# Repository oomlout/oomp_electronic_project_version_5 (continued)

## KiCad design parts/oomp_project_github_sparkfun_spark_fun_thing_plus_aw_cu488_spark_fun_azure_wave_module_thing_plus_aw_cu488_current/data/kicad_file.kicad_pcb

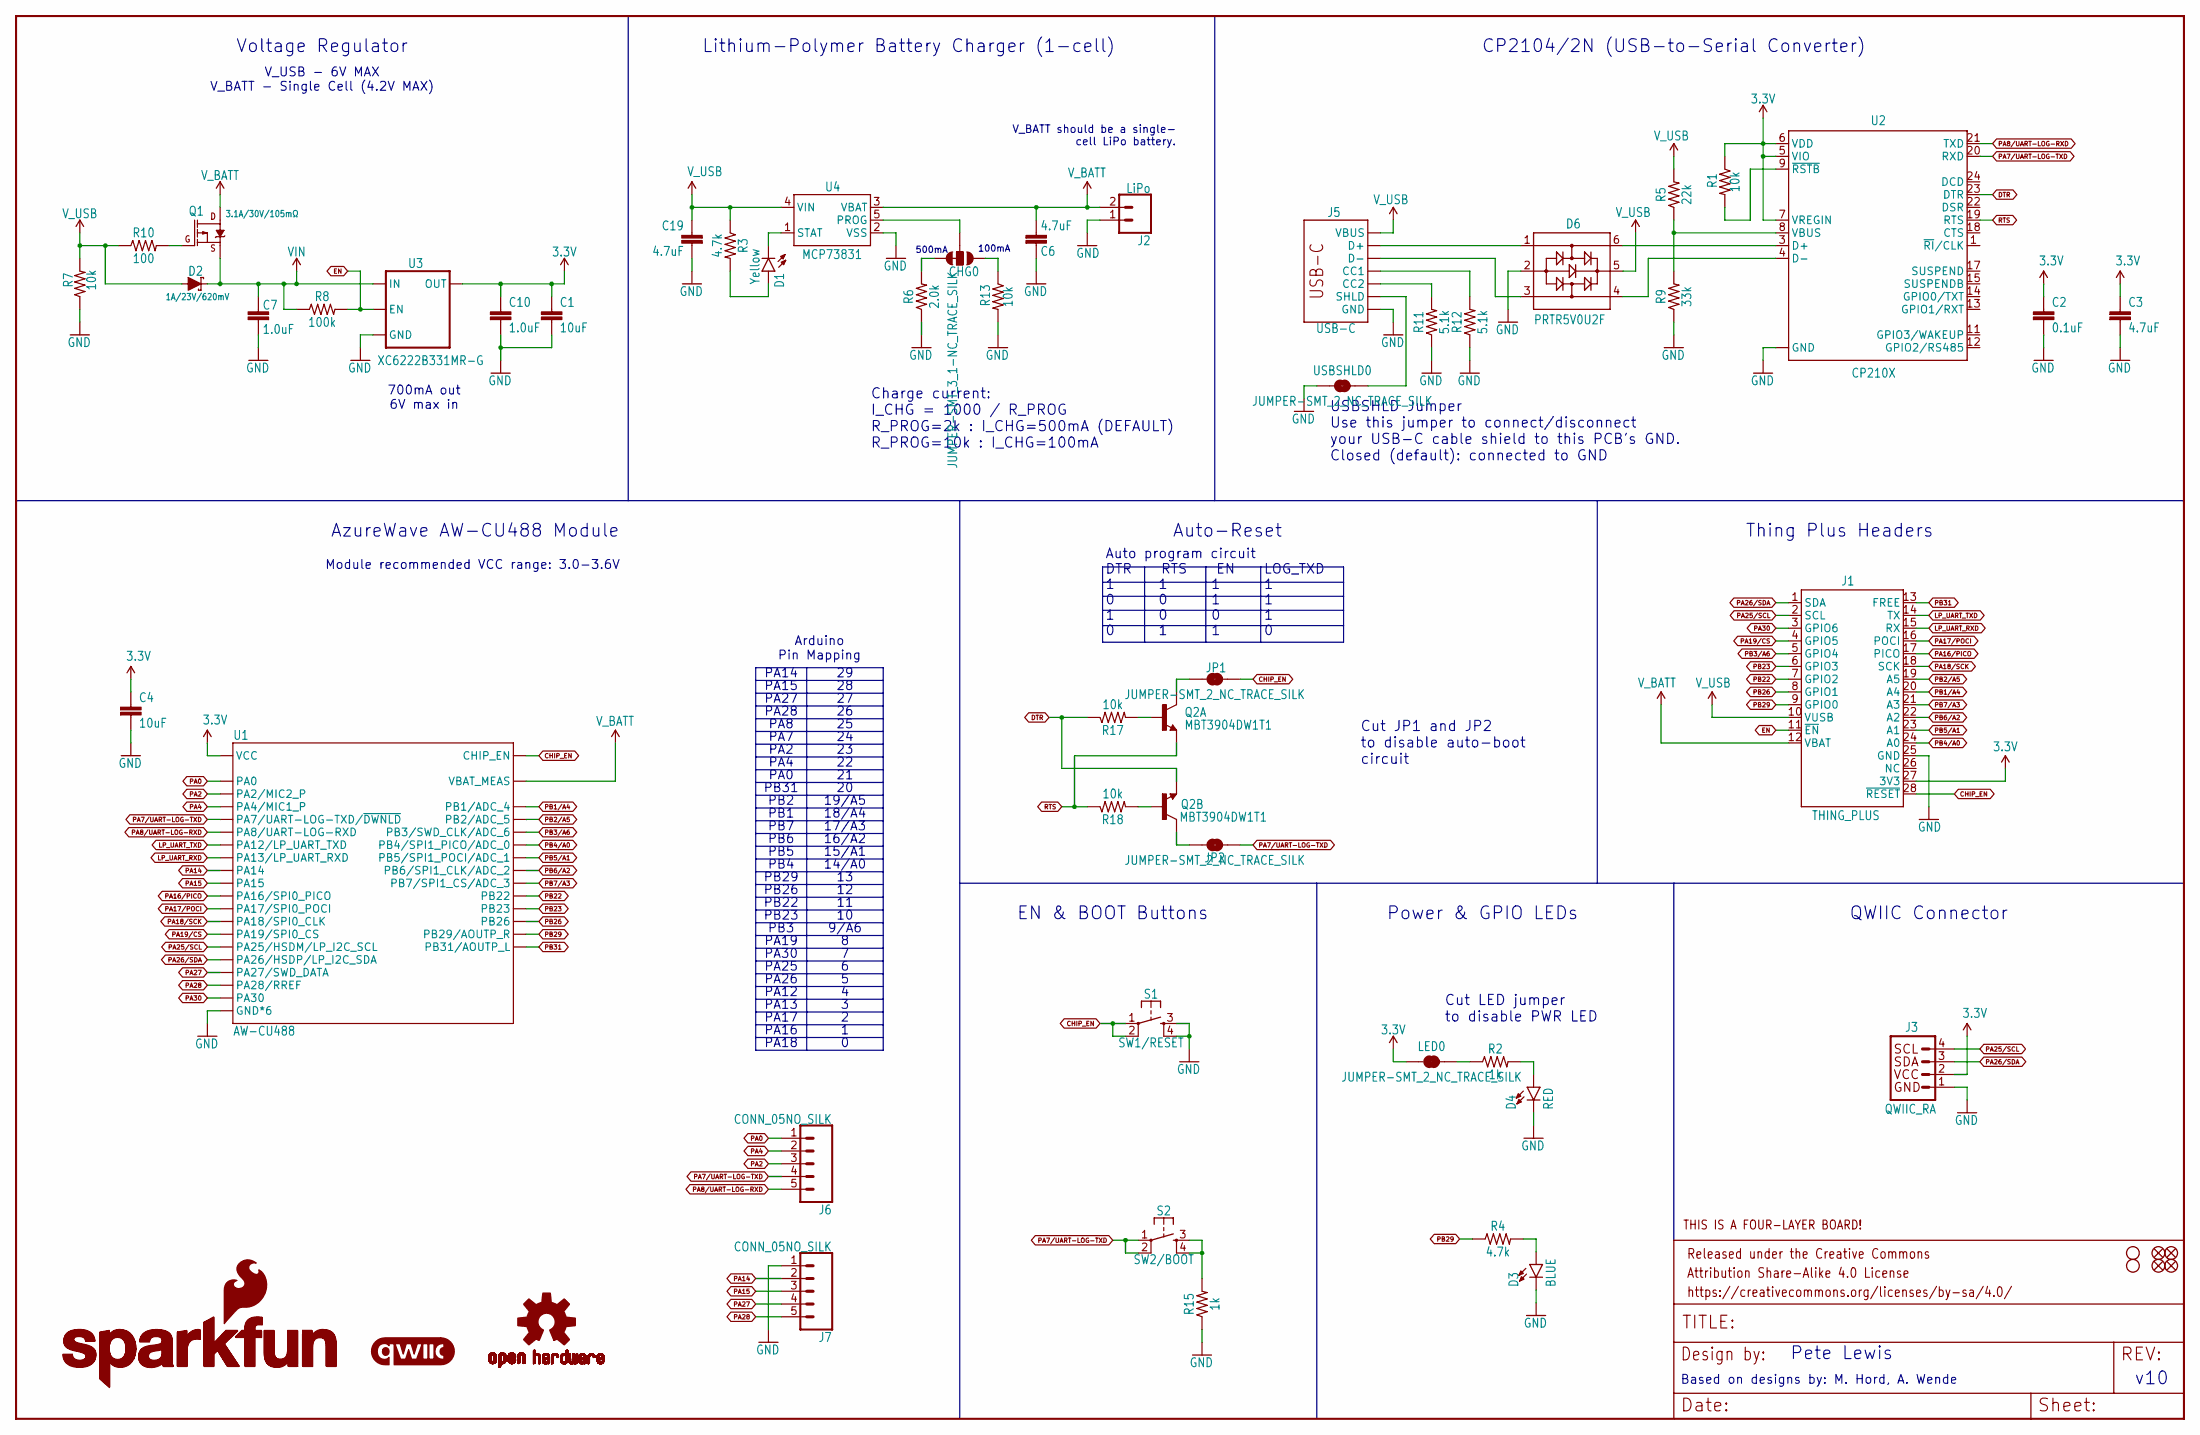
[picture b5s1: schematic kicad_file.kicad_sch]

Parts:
C1: 10uF; 0402-TIGHT
C2: 0.1uF; 0402-TIGHT
C3, C6, C19: 4.7uF; 0402-TIGHT
C4: 10uF; 0603
C7, C10: 1.0uF; 0402-TIGHT
CHG0: JUMPER-SMT_3_1-NC_TRACE_SILK; SMT-JUMPER_3_1-NC_TRACE_SILK
D1: Yellow; LED-0603
D2: 1A/23V/620mV; SOD-323
D3: BLUE; LED-0603
D4: RED; LED-0603
D6: PRTR5V0U2F; SOT886
FD1, FD2, FD3, FD4: FIDUCIALUFIDUCIAL; FIDUCIAL-MICRO
FRAME1: FRAME-LEDGER; CREATIVE_COMMONS
H1, H2: STAND-OFF
J1: THING_PLUS
J2: LiPo; JST-2-SMD
J3: QWIIC_RA; JST04_1MM_RA
J5: USB-C; USB-C-16P-4LAYER-ISOLATED
J6, J7: CONN_05NO_SILK; 1X05_NO_SILK
JP1, JP2: JUMPER-SMT_2_NC_TRACE_SILK; SMT-JUMPER_2_NC_TRACE_SILK
LED0: JUMPER-SMT_2_NC_TRACE_SILK; SMT-JUMPER_2_NC_TRACE_SILK
LOGO1: SFE_LOGO_NAME.1_INCH; SFE_LOGO_NAME_.1
LOGO2: OSHW-LOGOMINI; OSHW-LOGO-MINI
LOGO3: SFE_LOGO_NAME_FLAME.1_INCH; SFE_LOGO_NAME_FLAME_.1
LOGO4: FOUR_LAYER_WARNING
LOGO6: QWIIC_LOGO_4MM; QWIIC_4MM
Q1: 3.1A/30V/105mΩ; SOT23-3
Q2: MBT3904DW1T1; SC70-6
R1, R7, R13, R17, R18: 10k; 0402-TIGHT
R2, R15: 1k; 0402-TIGHT
R3, R4: 4.7k; 0402-TIGHT
R5: 22k; 0402-TIGHT
R6: 2.0k; 0603
R8: 100k; 0402-TIGHT
R9: 33k; 0402-TIGHT
R10: 100; 0402-TIGHT
R11, R12: 5.1k; 0402-TIGHT
S1: SW1/RESET; TACTILE_SWITCH_SMD_4.6X2.8MM
S2: SW2/BOOT; TACTILE_SWITCH_SMD_4.6X2.8MM
U1: AW-CU488; LGA150_AW-CU488
U2: CP210X; QFN24
U3: XC6222B331MR-G; SOT23-5
U4: MCP73831; SOT23-5
USBSHLD0: JUMPER-SMT_2_NC_TRACE_SILK; SMT-JUMPER_2_NC_TRACE_SILK

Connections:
3.3V: C1.1, C2.1, C3.1, C4.1, C10.1, J1.27 (3V3), J3.2, LED0.1, R1.1, U1.F1 (VCC), U2.5 (VIO), U2.6 (VDD), U2.7 (VREGIN), U3.5 (OUT)
CC1: J5.A5 (CC1), R12.2
CC2: J5.B5 (CC2), R11.2
CHG: D1.C, U4.1 (STAT)
CHIP_EN: J1.28 (~RESET), JP1.2, S1.1, S1.2, U1.K11 (CHIP_EN)
DTR: Q2.1 (E), R17.1, U2.23 (DTR)
EN: J1.11 (~EN), R8.2, U3.3 (EN)
GND: C1.2, C2.2, C3.2, C4.2, C6.2, C7.2, C10.2, C19.2, D3.C, D4.C, D6.2, J1.25 (GND), J2.1 (2), J3.1, J5.GND, J5.GND2 (GND), J7.1, R6.1, R7.1, R9.1, R11.1, R12.1, R13.2, R15.1, S1.3, S1.4, U1.A1 (GND*6), U1.A2 (GND*6), U1.A14 (GND*6), U1.A15 (GND*6), U1.B14 (GND*6), U1.B15 (GND*6), U1.C3 (GND*6), U1.C4 (GND*6), U1.C5 (GND*6), U1.C6 (GND*6), U1.C7 (GND*6), U1.C8 (GND*6), U1.C9 (GND*6), U1.C10 (GND*6), U1.C11 (GND*6), U1.C12 (GND*6), U1.C13 (GND*6), U1.C14 (GND*6), U1.C15 (GND*6), U1.D3 (GND*6), U1.D4 (GND*6), U1.D5 (GND*6), U1.D6 (GND*6), U1.D7 (GND*6), U1.D8 (GND*6), U1.D9 (GND*6), U1.D10 (GND*6), U1.D11 (GND*6), U1.D12 (GND*6), U1.D13 (GND*6), U1.D14 (GND*6), U1.D15 (GND*6), U1.E1 (GND*6), U1.E2 (GND*6), U1.E3 (GND*6), U1.E4 (GND*6), U1.E5 (GND*6), U1.E6 (GND*6), U1.E7 (GND*6), U1.E8 (GND*6), U1.E9 (GND*6), U1.E10 (GND*6), U1.E11 (GND*6), U1.E12 (GND*6), U1.E13 (GND*6), U1.E14 (GND*6), U1.E15 (GND*6), U1.F2 (GND*6), U1.F3 (GND*6), U1.F4 (GND*6), U1.F5 (GND*6), U1.F6 (GND*6), U1.F7 (GND*6), U1.F8 (GND*6), U1.F9 (GND*6), U1.F10 (GND*6), U1.F11 (GND*6), U1.F12 (GND*6), U1.F13 (GND*6), U1.F14 (GND*6), U1.F15 (GND*6), U1.G1 (GND*6), U1.G2 (GND*6), U1.G3 (GND*6), U1.G4 (GND*6), U1.G5 (GND*6), U1.G6 (GND*6), U1.G7 (GND*6), U1.G8 (GND*6), U1.G9 (GND*6), U1.G10 (GND*6), U1.G11 (GND*6), U1.G12 (GND*6), U1.G13 (GND*6), U1.G14 (GND*6), U1.G15 (GND*6), U1.H3 (GND*6), U1.H4 (GND*6), U1.H5 (GND*6), U1.H6 (GND*6), U1.H7 (GND*6), U1.H8 (GND*6), U1.H9 (GND*6), U1.H10 (GND*6), U1.H11 (GND*6), U1.H12 (GND*6), U1.H13 (GND*6), U1.H14 (GND*6), U1.H15 (GND*6), U1.J14 (GND*6), U1.J15 (GND*6), U1.K3 (GND*6), U1.K4 (GND*6), U1.K14 (GND*6), U1.K15 (GND*6), U2.2 (GND), U2.PAD (GND), U3.2 (GND), U4.2 (VSS), USBSHLD0.1
LP_UART_RXD: J1.15 (RX), U1.B13 (PA13/LP_UART_RXD)
LP_UART_TXD: J1.14 (TX), U1.A13 (PA12/LP_UART_TXD)
unnamed: R1.2, U2.9 (~RSTB)
unnamed: D3.A, R4.2
unnamed: Q2.5 (B), R17.2
unnamed: R5.1, R9.2, U2.8 (VBUS)
unnamed: Q2.2 (B), R18.2
unnamed: JP1.1, Q2.3 (C)
unnamed: Q1.1 (G), R10.2
unnamed: R15.2, S2.3, S2.4
unnamed: CHG0.2, U4.5 (PROG)
unnamed: JP2.1, Q2.6 (C)
unnamed: CHG0.1, R13.1
unnamed: LED0.2, R2.1
unnamed: CHG0.3, R6.2
unnamed: D4.A, R2.2
unnamed: D6.6, U2.3 (D+)
unnamed: D6.1, J5.A6 (D+), J5.B6 (D+)
unnamed: D1.A, R3.2
unnamed: D6.4, U2.4 (D-)
unnamed: D6.3, J5.A7 (D-), J5.B7 (D-)
PA0: J6.1, U1.K8 (PA0)
PA2: J6.3, U1.K10 (PA2/MIC2_P)
PA4: J6.2, U1.K9 (PA4/MIC1_P)
PA7/UART-LOG-TXD: J6.4, JP2.2, S2.1, S2.2, U1.K12 (PA7/UART-LOG-TXD/~DWNLD), U2.20 (RXD)
PA8/UART-LOG-RXD: J6.5, U1.K13 (PA8/UART-LOG-RXD), U2.21 (TXD)
PA14: J7.2, U1.A12 (PA14)
PA15: J7.3, U1.B12 (PA15)
PA16/PICO: J1.17 (PICO), U1.A11 (PA16/SPI0_PICO)
PA17/POCI: J1.16 (POCI), U1.B11 (PA17/SPI0_POCI)
PA18/SCK: J1.18 (SCK), U1.A10 (PA18/SPI0_CLK)
PA19/CS: J1.4 (GPIO5), U1.B10 (PA19/SPI0_CS)
PA25/SCL: J1.2 (SCL), J3.4, U1.A5 (PA25/HSDM/LP_I2C_SCL)
PA26/SDA: J1.1 (SDA), J3.3, U1.A6 (PA26/HSDP/LP_I2C_SDA)
PA27: J7.4, U1.A9 (PA27/SWD_DATA)
PA28: J7.5, U1.A7 (PA28/RREF)
PA30: J1.3 (GPIO6), U1.A8 (PA30)
PB1/A4: J1.20 (A4), U1.A3 (PB1/ADC_4)
PB2/A5: J1.19 (A5), U1.A4 (PB2/ADC_5)
PB3/A6: J1.5 (GPIO4), U1.B1 (PB3/SWD_CLK/ADC_6)
PB4/A0: J1.24 (A0), U1.B2 (PB4/SPI1_PICO/ADC_0)
PB5/A1: J1.23 (A1), U1.C1 (PB5/SPI1_POCI/ADC_1)
PB6/A2: J1.22 (A2), U1.C2 (PB6/SPI1_CLK/ADC_2)
PB7/A3: J1.21 (A3), U1.D1 (PB7/SPI1_CS/ADC_3)
PB22: J1.7 (GPIO2), U1.K1 (PB22)
PB23: J1.6 (GPIO3), U1.K2 (PB23)
PB26: J1.8 (GPIO1), U1.K5 (PB26)
PB29: J1.9 (GPIO0), R4.1, U1.K6 (PB29/AOUTP_R)
PB31: J1.13 (FREE), U1.K7 (PB31/AOUTP_L)
RTS: Q2.4 (E), R18.1, U2.19 (RTS)
USB_SHLD: J5.SHLD1 (SHLD), J5.SHLD2 (SHLD), J5.SHLD3 (SHLD), J5.SHLD4 (SHLD), J5.SHLD5 (SHLD), J5.SHLD6 (SHLD), J5.SHLD7 (SHLD), J5.SHLD8 (SHLD), USBSHLD0.2
VIN: C7.1, D2.C, Q1.2 (S), R8.1, U3.1 (IN)
V_BATT: C6.1, J1.12 (VBAT), J2.2 (1), Q1.3 (D), U1.D2 (VBAT_MEAS), U4.3 (VBAT)
V_USB: C19.1, D2.A, D6.5, J1.10 (VUSB), J5.VBUS1 (VBUS), J5.VBUS2 (VBUS), R3.1, R5.2, R7.2, R10.1, U4.4 (VIN)

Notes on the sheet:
PA4
PB7
PA18
500mA
PB26
PB5
PA16
PB6
Power & GPIO LEDs
v10
PA15
Arduino Pin Mapping
Lithium-Polymer Battery Charger (1-cell)
100mA
PA27
Cut LED jumper to disable PWR LED
Cut JP1 and JP2 to disable auto-boot circuit
V_BATT should be a single- cell LiPo battery.
EN & BOOT Buttons
PA30
PB4
Module recommended VCC range: 3.0-3.6V
19/A5
Voltage Regulator
Pete Lewis
700mA out 6V max in
PA7
9/A6
PB29
PB22
PB31
PA28
PB23
15/A1
PA12
16/A2
QWIIC Connector
Auto-Reset
CP2104/2N (USB-to-Serial Converter)
USBSHLD Jumper Use this jumper to connect/disconnect your USB-C cable shield to this PCB's GND. Closed (default): connected to GND

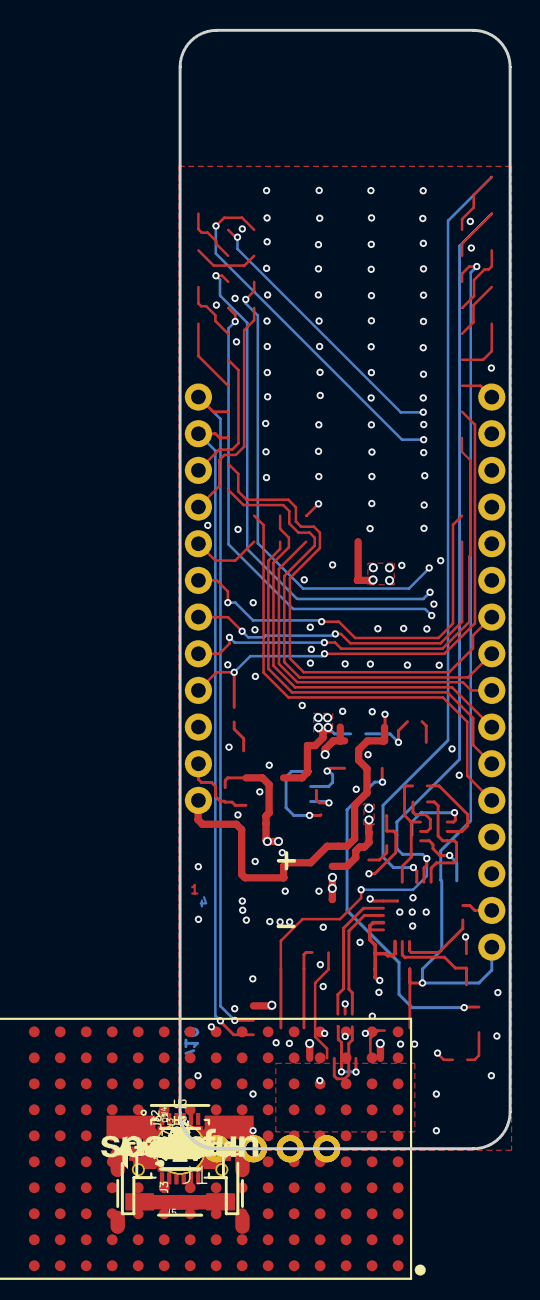
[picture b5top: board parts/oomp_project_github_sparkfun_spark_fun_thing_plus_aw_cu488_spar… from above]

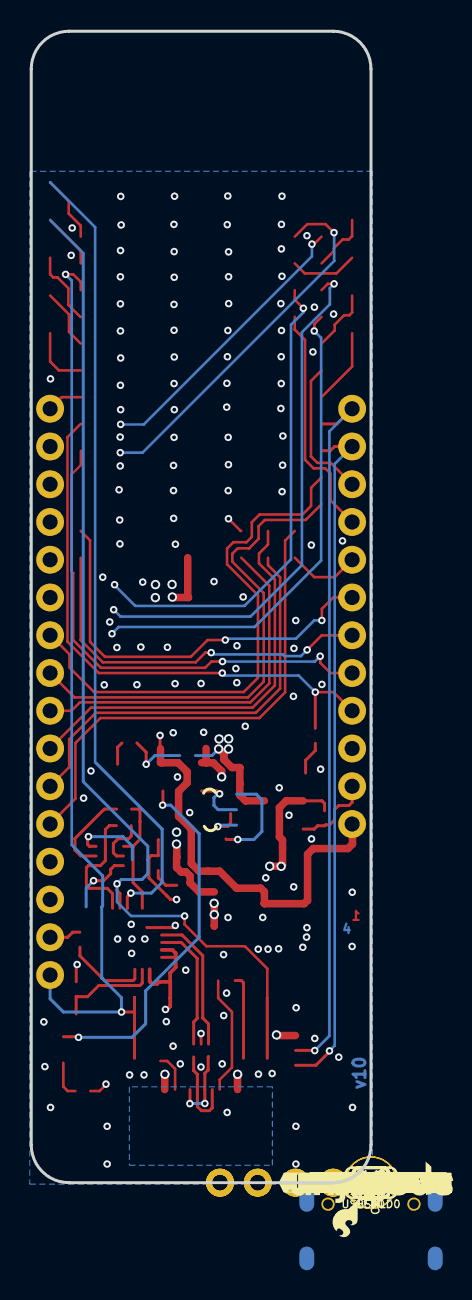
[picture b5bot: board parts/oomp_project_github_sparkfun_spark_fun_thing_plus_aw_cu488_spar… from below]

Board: 4 copper layers, 22.9 x 77.5 mm, 128 parts (57 on the bottom side), 62 nets.

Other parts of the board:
U$1: #10#30
U$2: BOOT0
U$3, U$78: CHG0
U$4: #500#0
U$5: #11#30
U$6, U$8: AZUREWAVE0
U$7: 1330
U$9, U$27: AW#CU488_0
U$10, U$62: THING_PLUS_0
U$11: MA0
U$12: #12#30
U$14: #13#30
U$15: #JP1#1
U$16: #0#1
U$18: #A0#30
U$19: #JP2#4
U$20: #USBSHLD#GND#3
U$23: PWR0
U$29: #LED#0
U$32, U$86: #GND#0
U$41: #VUSB#0
U$42: #VBAT#0
U$43: #EN#0
U$45: #3V3#0
U$46: ##RESET##0
U$48: #4#TX1#14
U$49: #3#RX1#14
U$50: #2#POCI#14
U$53: #A1#6
U$54: #A2#6
U$55: #A3#6
U$56: #A4#6
U$57: #A5#6
U$59: ORDERING_INSTRUCTIONS
U$60: #100#0
U$64: #1#PICO#14
U$67: #13#14
U$68: #12#14
U$69: #11#14
U$70: #10#14
U$71: #9#A6#14
U$72: #8#CS#14
U$73: #7#14
U$74: #6#SCL#14
U$75: #5#SDA#14
U$76: #0#SCK#14
U$77: #14#A0#15
U$79: RESET0
U$80: #15#A1#15
U$81: #16#A2#16
U$82: #17#A3#17
U$83: #18#A4#18
U$84: #19#A5#19
U$85: #20#20
U$87: #21#21
U$88: #22#22
U$89: #23#23
U$90: #24#TX#24
U$91: #25#RX#25
U$92: #26#26
U$93: #27#27
U$94: #28#28
U$95: #29#29

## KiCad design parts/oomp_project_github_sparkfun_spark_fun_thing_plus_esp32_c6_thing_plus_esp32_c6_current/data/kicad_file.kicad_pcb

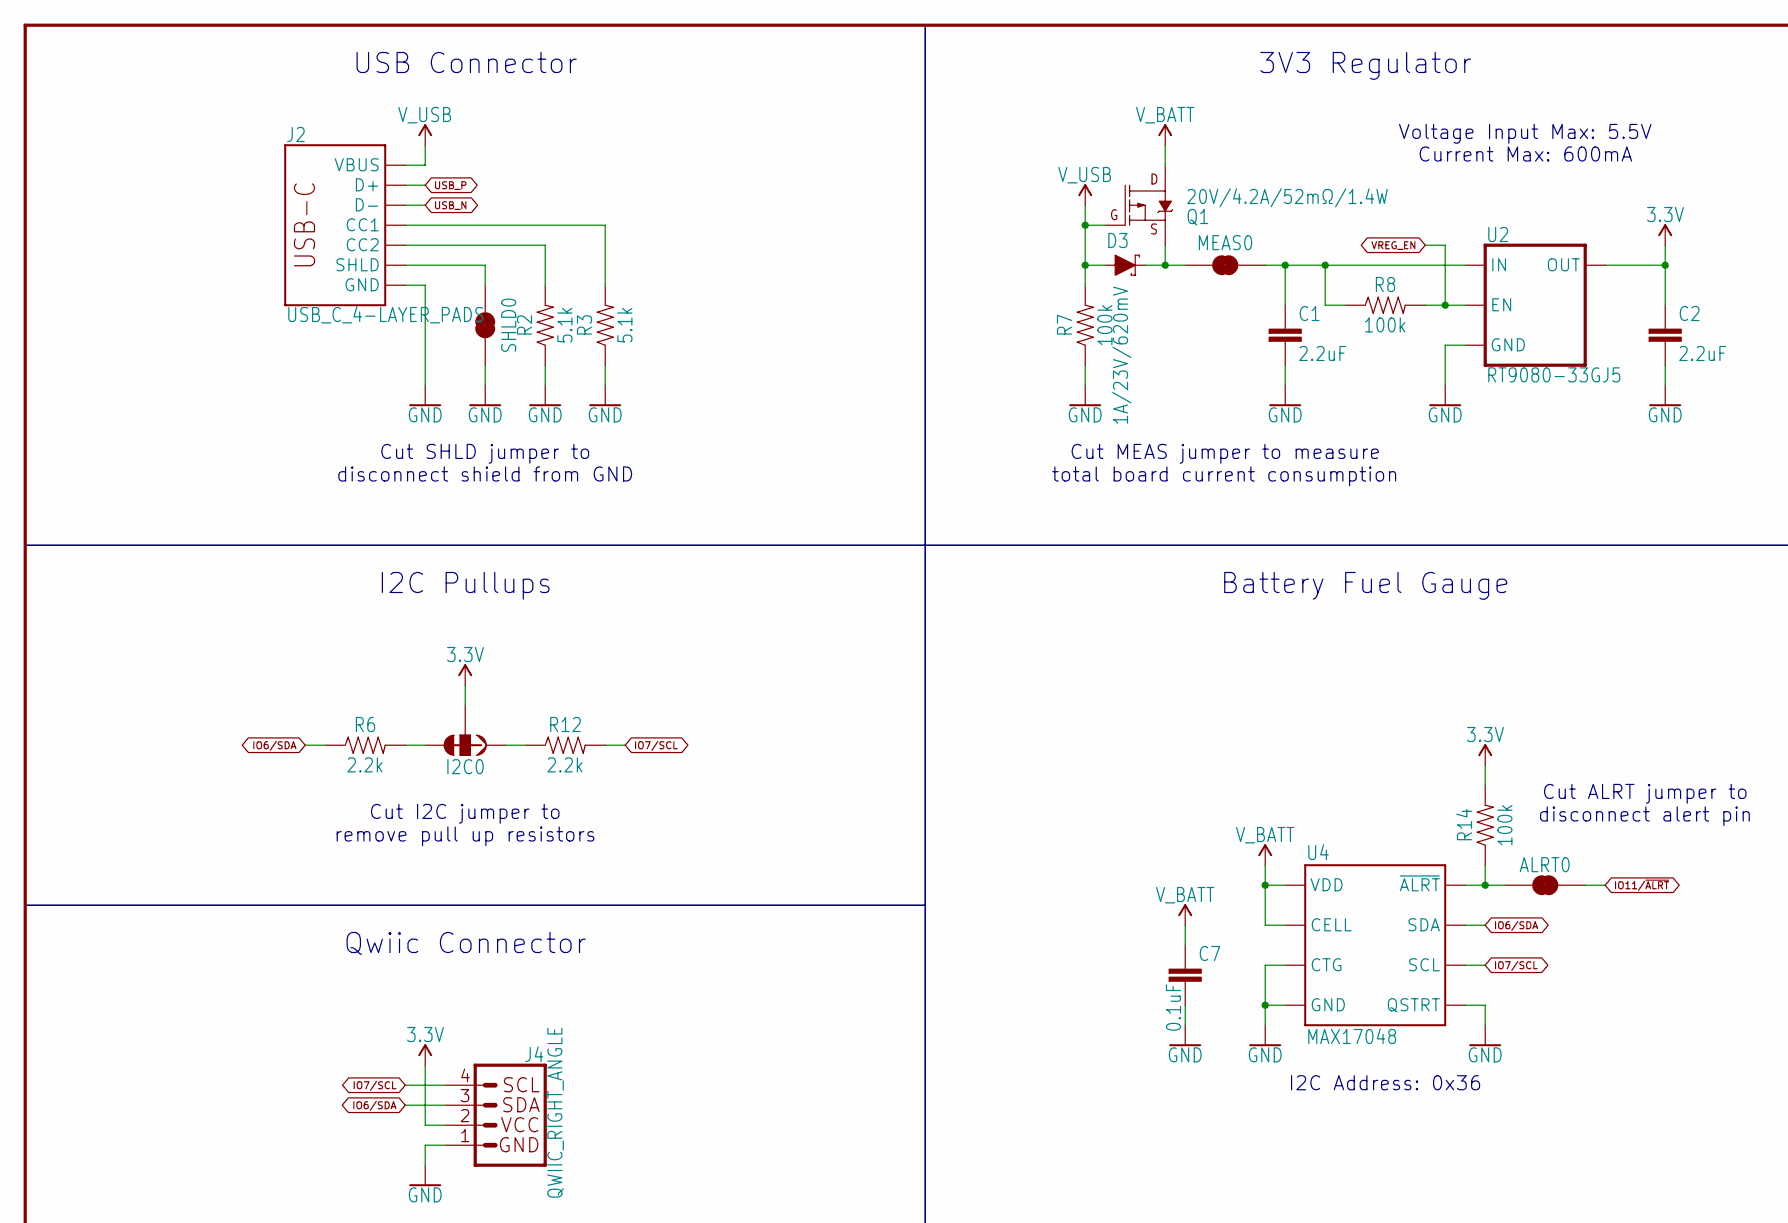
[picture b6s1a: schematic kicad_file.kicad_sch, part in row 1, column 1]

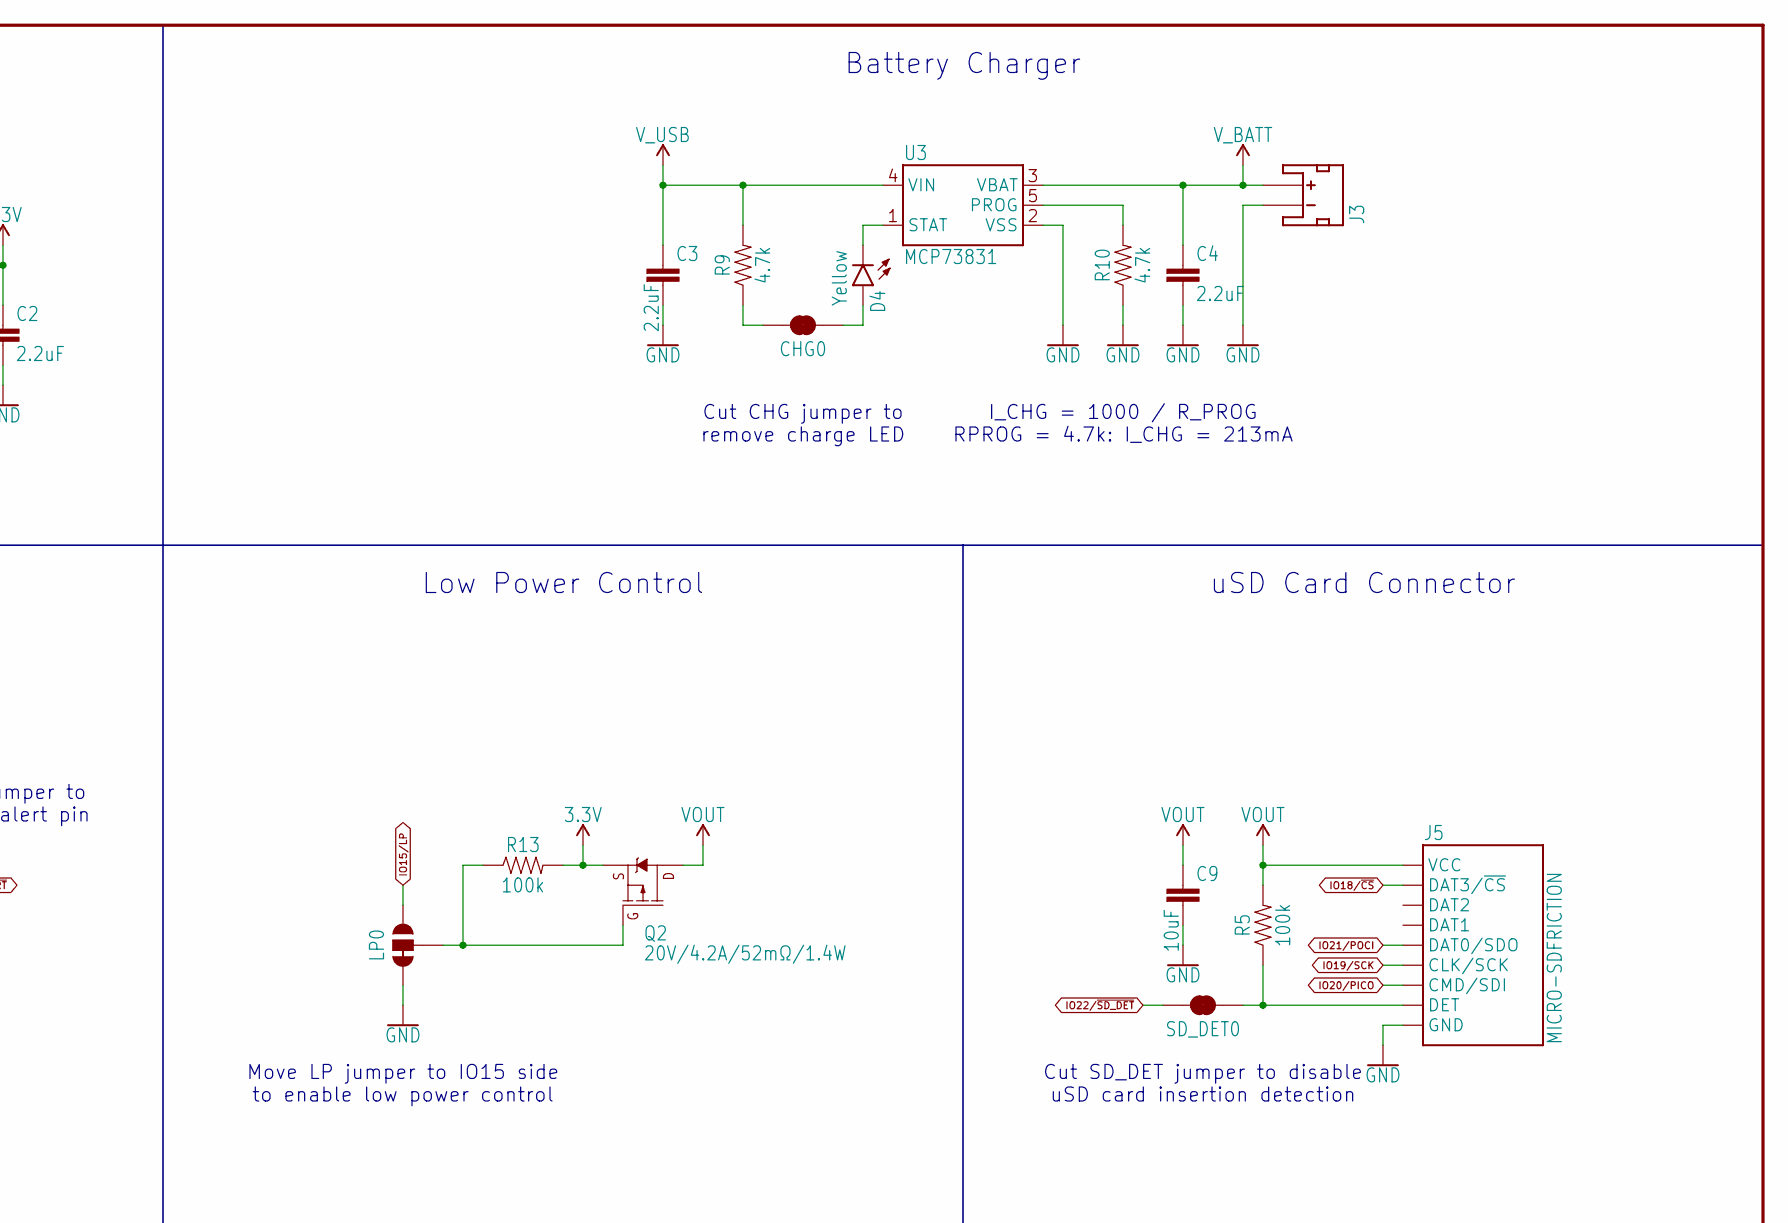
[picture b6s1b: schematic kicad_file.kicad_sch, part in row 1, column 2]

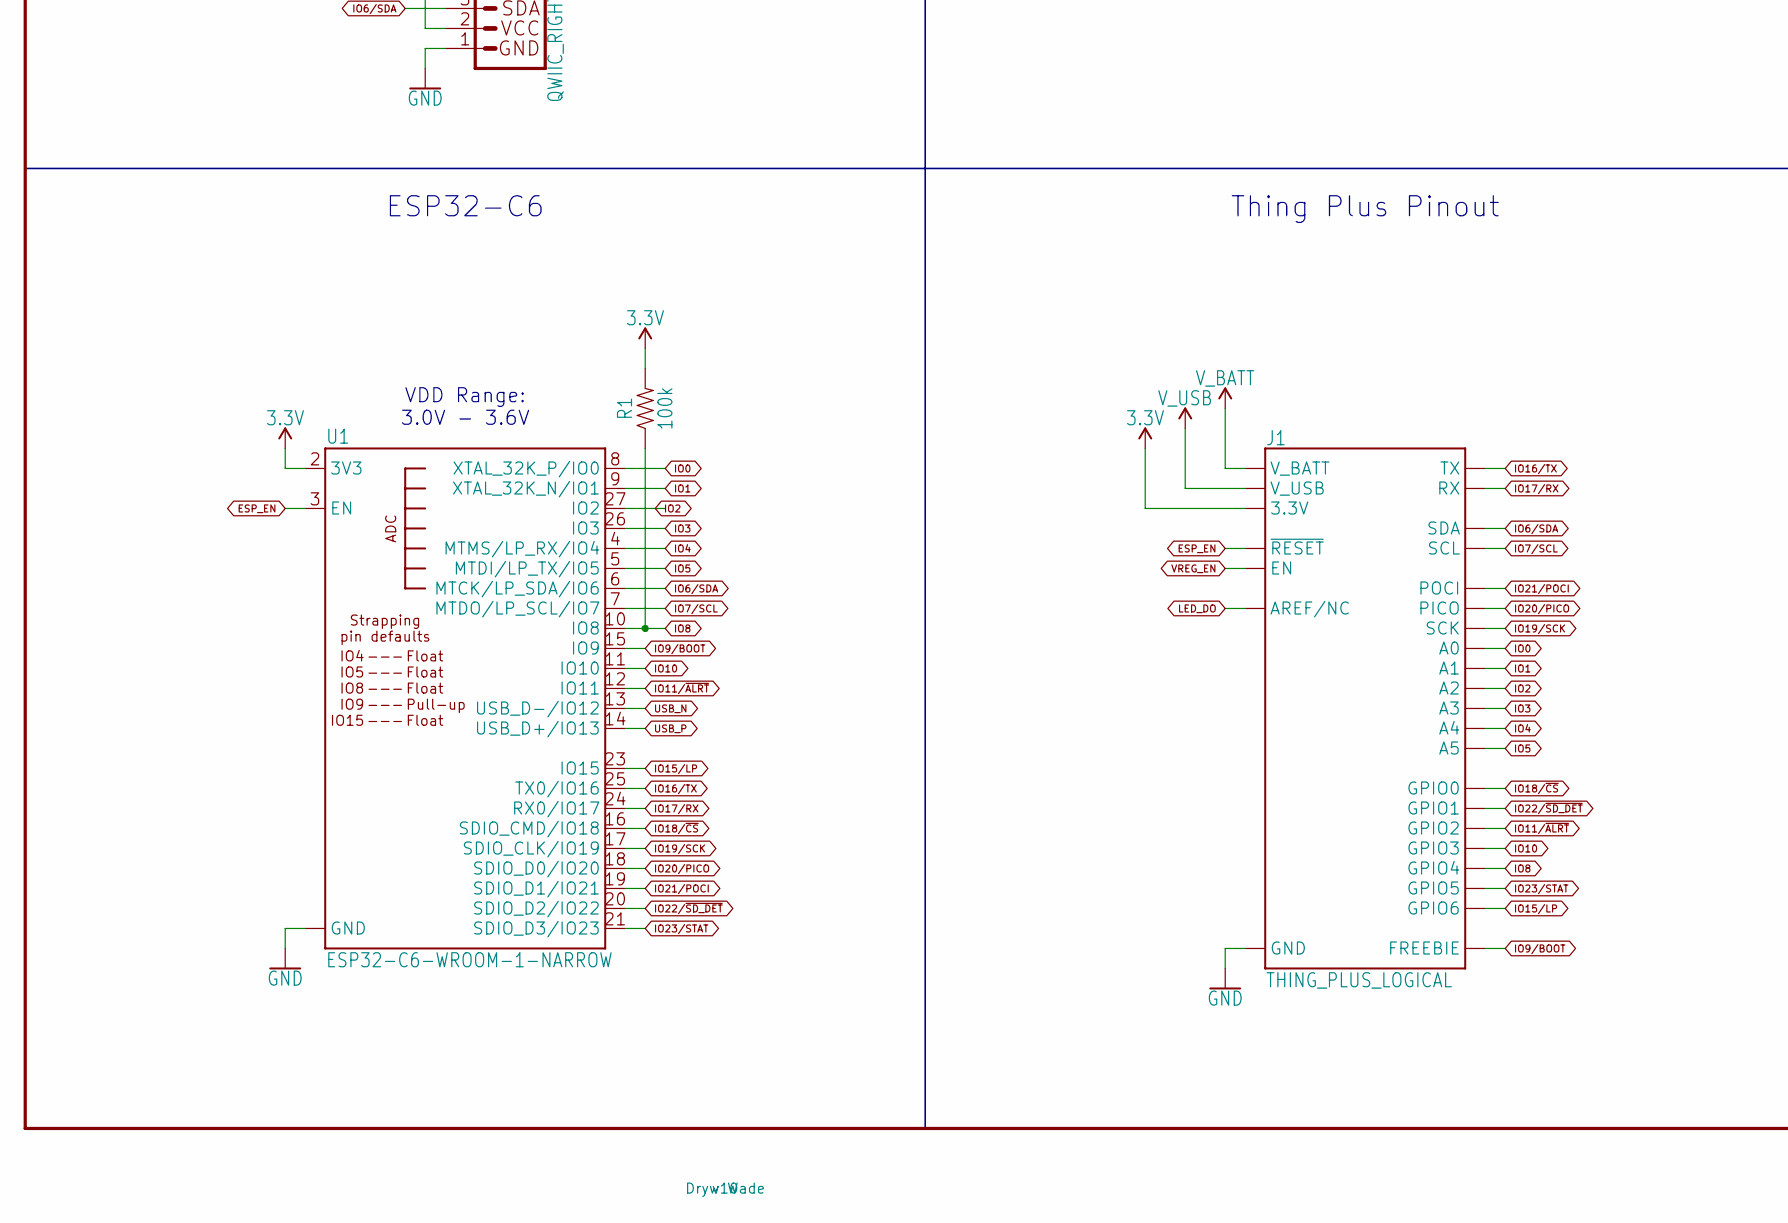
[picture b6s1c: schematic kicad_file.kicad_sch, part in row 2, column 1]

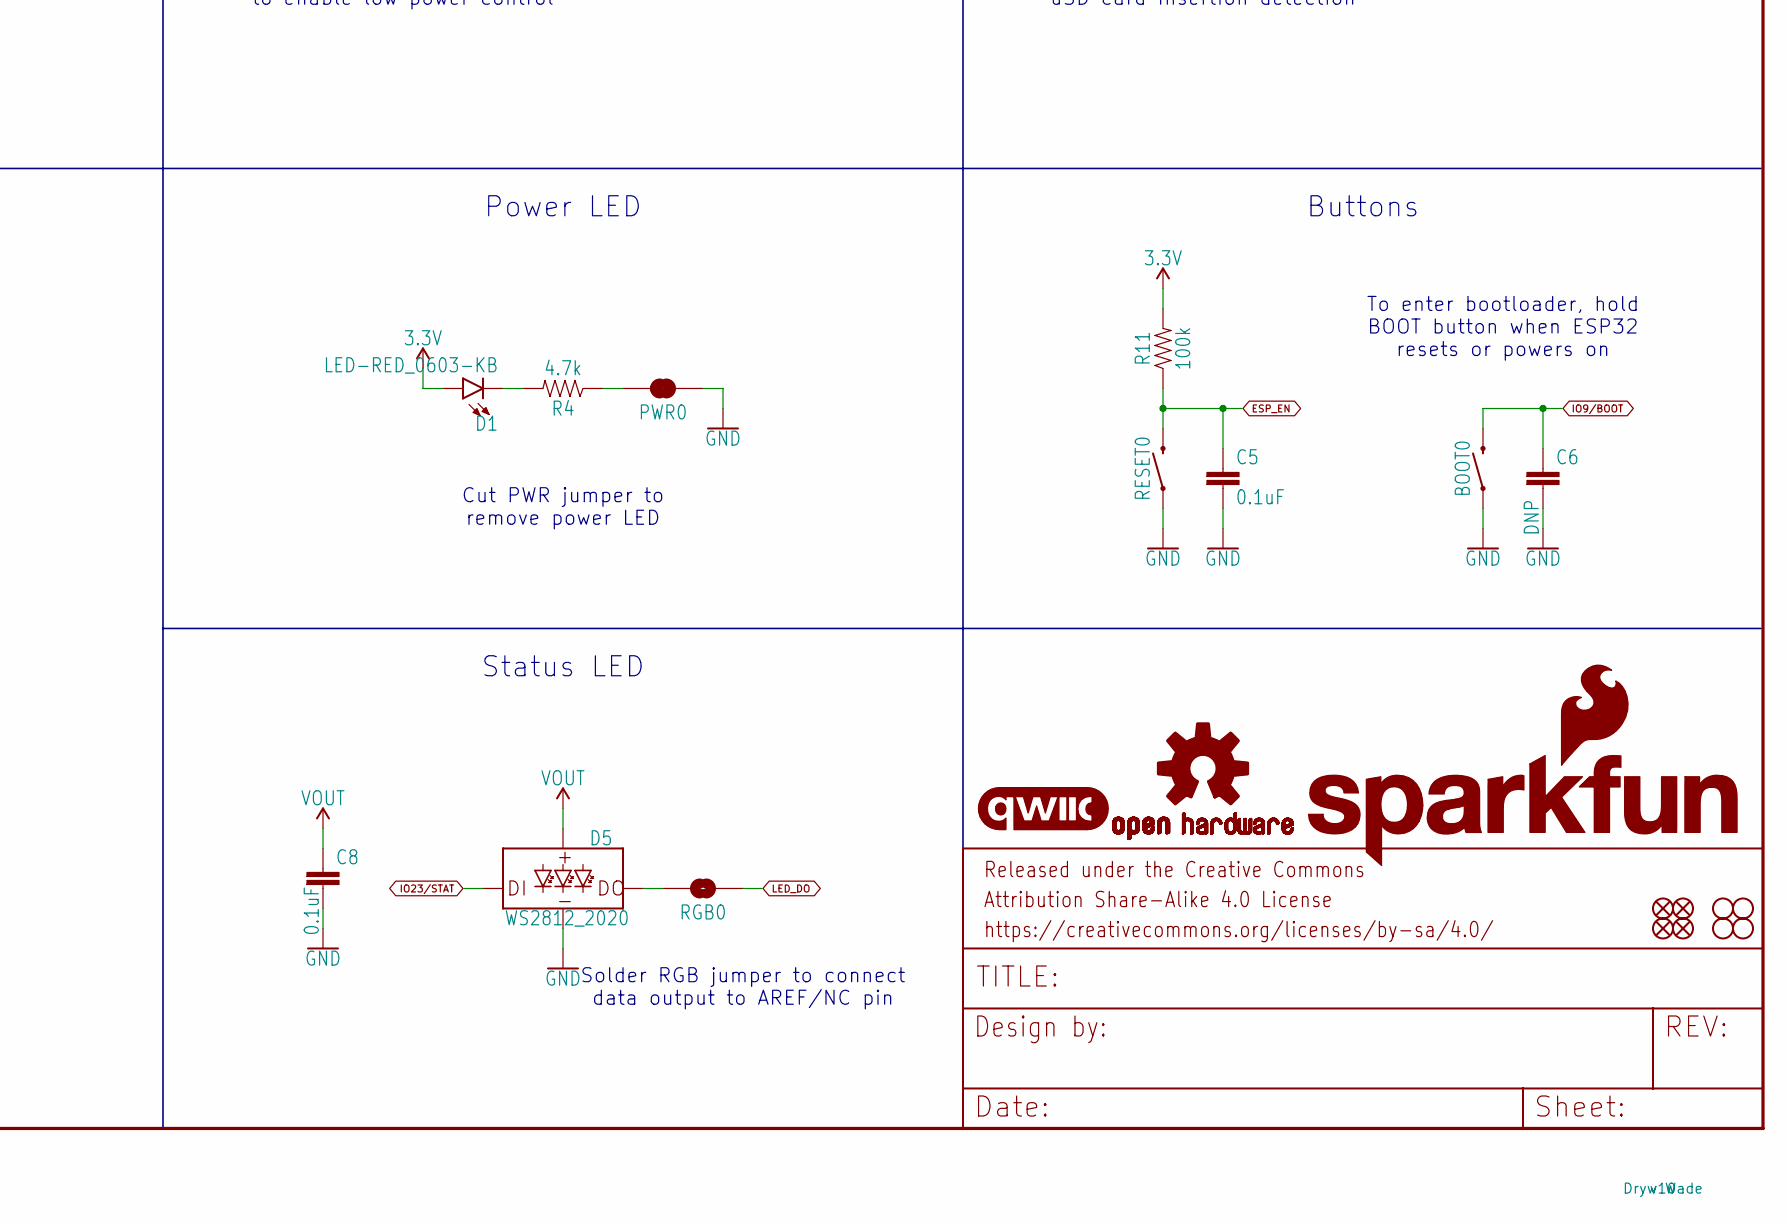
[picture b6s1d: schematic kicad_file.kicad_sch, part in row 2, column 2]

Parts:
ALRT0: JUMPER-SMT_2_NC_TRACE_SILK; SMT-JUMPER_2_NC_TRACE_SILK
BOOT0: MOMENTARY-SWITCH-SPST-SMD-4.6X2.8MM; TACTILE_SWITCH_SMD_4.6X2.8MM
C1, C2, C3, C4: 2.2uF; 0603
C5, C7, C8: 0.1uF; 0603
C6: DNP; 0603
C9: 10uF; 0603
CHG0: JUMPER-SMT_2_NC_TRACE_SILK; SMT-JUMPER_2_NC_TRACE_SILK
D1: LED-RED_0603-KB; LED-0603
D3: 1A/23V/620mV; SOD-323
D4: Yellow; LED-0603
D5: WS2812_2020; WS2812-2020
FD1, FD2, FD3, FD4: FIDUCIALUFIDUCIAL; FIDUCIAL-MICRO
FRAME1: FRAME-LEDGER; CREATIVE_COMMONS
H1, H2, H3, H4: STAND-OFF
I2C0: JUMPER-SMT_3_2-NC_TRACE_SILK; SMT-JUMPER_3_2-NC_TRACE_SILK
J1: THING_PLUS_LOGICAL; THING_PLUS
J2: USB_C_4-LAYER_PADS; USB-C-16P_4LAYER-PADS
J3: JST_2MM_MALE; JST-2-SMD
J4: QWIIC_RIGHT_ANGLE; JST04_1MM_RA
J5: MICRO-SDFRICTION; MICROSD_TINY
LOGO1: SFE_LOGO_NAME_FLAME.1_INCH; SFE_LOGO_NAME_FLAME_.1
LOGO2: QWIIC_LOGO_4MM; QWIIC_4MM
LOGO3: OSHW-LOGOM; OSHW-LOGO-M
LP0: JUMPER-SMT_3_1-NC_TRACE_SILK; SMT-JUMPER_3_1-NC_TRACE_SILK
MEAS0: JUMPER-COMBO_2_NC_TRACE; COMBO-JUMPER_2_NC_TRACE
PWR0: JUMPER-SMT_2_NC_TRACE_SILK; SMT-JUMPER_2_NC_TRACE_SILK
Q1, Q2: 20V/4.2A/52mΩ/1.4W; SOT23-3
R1, R5, R7, R8, R11, R13, R14: 100k; 0603
R2, R3: 5.1k; 0603
R4, R9, R10: 4.7k; 0603
R6, R12: 2.2k; 0603
RESET0: MOMENTARY-SWITCH-SPST-SMD-4.6X2.8MM; TACTILE_SWITCH_SMD_4.6X2.8MM
RGB0: JUMPER-SMT_2_NO_SILK; SMT-JUMPER_2_NO_SILK
SD_DET0: JUMPER-SMT_2_NC_TRACE_SILK; SMT-JUMPER_2_NC_TRACE_SILK
SHLD0: JUMPER-SMT_2_NC_TRACE_SILK; SMT-JUMPER_2_NC_TRACE_SILK
U1: ESP32-C6-WROOM-1-NARROW
U2: RT9080-33GJ5; SOT23-5
U3: MCP73831; SOT23-5
U4: MAX17048; DFN-8

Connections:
3.3V: C2.1, D1.A, I2C0.2, J1.27 (3.3V), J4.2, Q2.2 (S), R1.2, R11.2, R13.2, R14.2, U1.2 (3V3), U2.5 (OUT)
ESP_EN: C5.1, J1.28 (~RESET), R11.1, RESET0.3 (2), RESET0.4 (2), U1.3 (EN)
GND: BOOT0.1, BOOT0.2 (1), C1.2, C2.2, C3.2, C4.2, C5.2, C6.2, C7.2, C8.2, C9.2, D5.GND, J1.25 (GND), J2.GND, J2.GND2 (GND), J3.1 (-), J4.1, J5.6 (GND), J5.GND1 (GND), J5.GND2 (GND), J5.GND3 (GND), J5.GND4 (GND), J5.GND5 (GND), J5.GND6 (GND), LP0.3, PWR0.1, R2.1, R3.1, R7.1, R10.1, RESET0.1, RESET0.2 (1), SHLD0.2, U1.1 (GND), U1.28 (GND), U1.29 (GND), U1.30 (GND), U1.31 (GND), U1.32 (GND), U1.33 (GND), U1.34 (GND), U1.35 (GND), U1.36 (GND), U1.37 (GND), U2.2 (GND), U3.2 (VSS), U4.1 (CTG), U4.4 (GND), U4.6 (QSTRT), U4.9 (GND)
IO0: J1.24 (A0), U1.8 (XTAL_32K_P/IO0)
IO1: J1.23 (A1), U1.9 (XTAL_32K_N/IO1)
IO2: J1.22 (A2), U1.27 (IO2)
IO3: J1.21 (A3), U1.26 (IO3)
IO4: J1.20 (A4), U1.4 (MTMS/LP_RX/IO4)
IO5: J1.19 (A5), U1.5 (MTDI/LP_TX/IO5)
IO6/SDA: J1.1 (SDA), J4.3, R6.1, U1.6 (MTCK/LP_SDA/IO6), U4.8 (SDA)
IO7/SCL: J1.2 (SCL), J4.4, R12.2, U1.7 (MTDO/LP_SCL/IO7), U4.7 (SCL)
IO8: J1.5 (GPIO4), R1.1, U1.10 (IO8)
IO9/BOOT: BOOT0.3 (2), BOOT0.4 (2), C6.1, J1.13 (FREEBIE), U1.15 (IO9)
IO10: J1.6 (GPIO3), U1.11 (IO10)
IO11/~ALRT: ALRT0.2, J1.7 (GPIO2), U1.12 (IO11)
IO15/LP: J1.3 (GPIO6), LP0.1, U1.23 (IO15)
IO16/TX: J1.14 (TX), U1.25 (TX0/IO16)
IO17/RX: J1.15 (RX), U1.24 (RX0/IO17)
IO18/~CS: J1.9 (GPIO0), J5.2 (DAT3/~CS), U1.16 (SDIO_CMD/IO18)
IO19/SCK: J1.18 (SCK), J5.5 (CLK/SCK), U1.17 (SDIO_CLK/IO19)
IO20/PICO: J1.17 (PICO), J5.3 (CMD/SDI), U1.18 (SDIO_D0/IO20)
IO21/POCI: J1.16 (POCI), J5.7 (DAT0/SDO), U1.19 (SDIO_D1/IO21)
IO22/~SD_DET: J1.8 (GPIO1), SD_DET0.2, U1.20 (SDIO_D2/IO22)
IO23/STAT: D5.DI, J1.4 (GPIO5), U1.21 (SDIO_D3/IO23)
LED_DO: J1.26 (AREF/NC), RGB0.1
unnamed: D1.C, R4.2
unnamed: PWR0.2, R4.1
unnamed: J5.9 (DET), R5.1, SD_DET0.1
unnamed: D3.C, MEAS0.1, MEAS0.3 (1), Q1.2 (S)
unnamed: I2C0.3, R6.2
unnamed: I2C0.1, R12.1
unnamed: J2.B5 (CC2), R2.2
unnamed: J2.A5 (CC1), R3.2
unnamed: C1.1, MEAS0.2, MEAS0.4 (2), R8.1, U2.1 (IN)
unnamed: D4.C, U3.1 (STAT)
unnamed: CHG0.1, D4.A
unnamed: CHG0.2, R9.1
unnamed: R10.2, U3.5 (PROG)
unnamed: D5.DO, RGB0.2
unnamed: LP0.2, Q2.1 (G), R13.1
unnamed: ALRT0.1, R14.1, U4.5 (~ALRT)
SHLD: J2.SHLD1 (SHLD), J2.SHLD2 (SHLD), J2.SHLD3 (SHLD), J2.SHLD4 (SHLD), SHLD0.1
USB_N: J2.A7 (D-), J2.B7 (D-), U1.13 (USB_D-/IO12)
USB_P: J2.A6 (D+), J2.B6 (D+), U1.14 (USB_D+/IO13)
VOUT: C8.1, C9.1, D5.VCC, J5.4 (VCC), Q2.3 (D), R5.2
VREG_EN: J1.11 (EN), R8.2, U2.3 (EN)
V_BATT: C4.1, C7.1, J1.12 (V_BATT), J3.2 (+), Q1.3 (D), U3.3 (VBAT), U4.2 (CELL), U4.3 (VDD)
V_USB: C3.1, D3.A, J1.10 (V_USB), J2.VBUS1 (VBUS), J2.VBUS2 (VBUS), Q1.1 (G), R7.2, R9.2, U3.4 (VIN)

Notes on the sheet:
Battery Fuel Gauge
Cut SHLD jumper to disconnect shield from GND
I_CHG = 1000 / R_PROG RPROG = 4.7k: I_CHG = 213mA
3V3 Regulator
Qwiic Connector
To enter bootloader, hold BOOT button when ESP32 resets or powers on
I2C Address: 0x36
Cut PWR jumper to remove power LED
Low Power Control
Power LED
Cut ALRT jumper to disconnect alert pin
I2C Pullups
Battery Charger
Buttons
Cut CHG jumper to remove charge LED
Cut I2C jumper to remove pull up resistors
Status LED
VDD Range: 3.0V - 3.6V
ESP32-C6
Move LP jumper to IO15 side to enable low power control
USB Connector
uSD Card Connector
Thing Plus Pinout
Voltage Input Max: 5.5V Current Max: 600mA
Cut SD_DET jumper to disable uSD card insertion detection
Cut MEAS jumper to measure total board current consumption
Solder RGB jumper to connect data output to AREF/NC pin

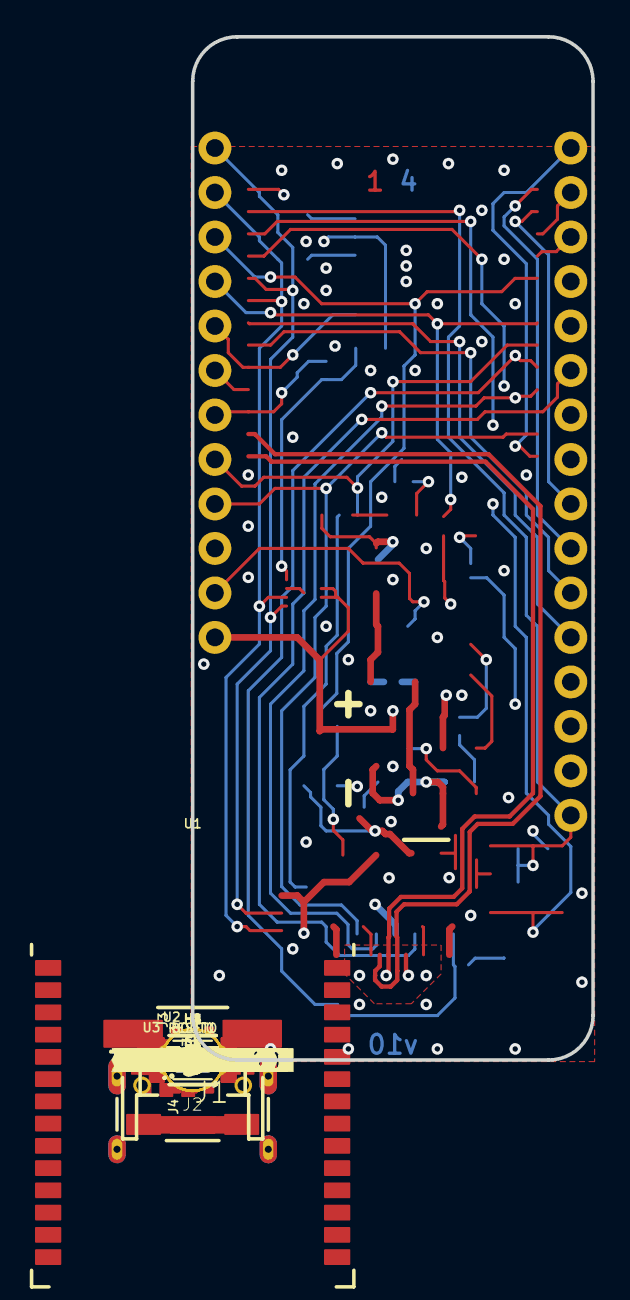
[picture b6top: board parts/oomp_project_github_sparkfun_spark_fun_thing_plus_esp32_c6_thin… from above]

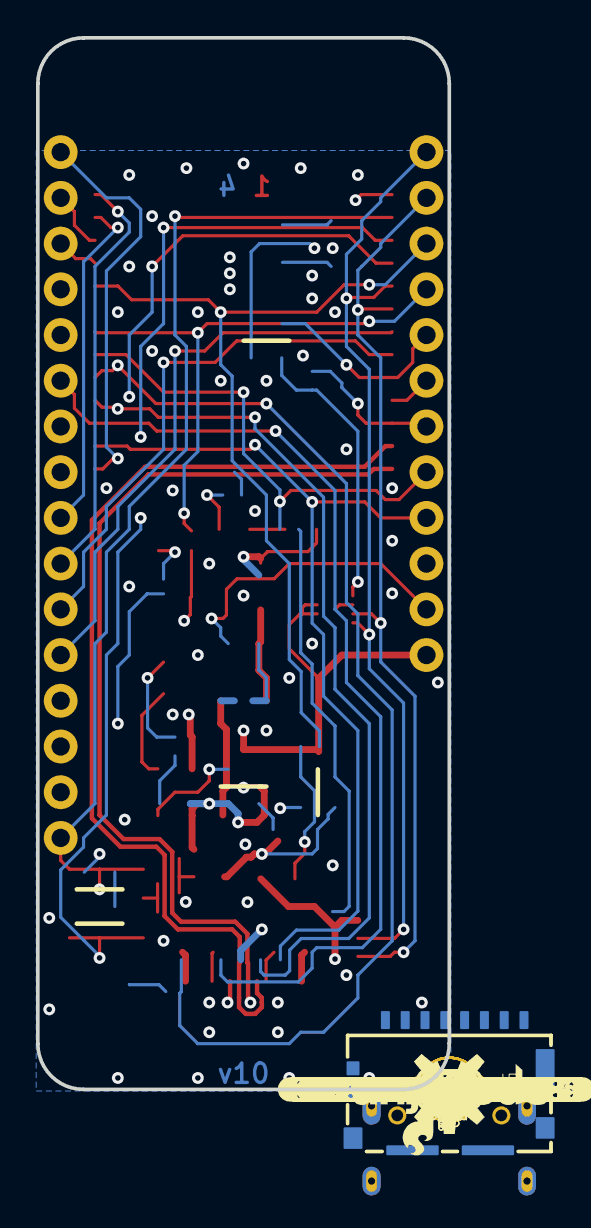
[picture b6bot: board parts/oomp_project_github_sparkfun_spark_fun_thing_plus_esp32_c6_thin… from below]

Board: 4 copper layers, 22.9 x 58.4 mm, 125 parts (69 on the bottom side), 48 nets.

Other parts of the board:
U$1: #SHLD#0
U$2: #I�C#0
U$3: #_IO18#0
U$4: #_VUSB#0
U$5: #_VBAT#0
U$6: #_EN#0
U$7: #IO3_#0
U$8: #IO2_#0
U$9: #IO1_#0
U$10: #IO0_#0
U$11: #GND_#0
U$12: #3V3_#0
U$13, U$37: ##RST#_#0
U$14: #SDA#IO6_#0
U$15: #SCL#IO7_#0
U$16: #_IO21#POCI#0
U$17: #LP#0
U$18: #IO8_#0
U$19: #IO10_#0
U$20: #IO11_#0
U$21: #_IO19#SCK#0
U$22: #IO18_#0
U$23: #_IO9#0
U$24: #_IO16#TX#0
U$25: #_IO17#RX#0
U$26: #_IO20#PICO#0
U$27: #IO15#0
U$28: #ALRT#0
U$29: #_IO5#0
U$30: #_IO4#0
U$31: #_IO3#0
U$32: #_IO2#0
U$33: #_IO1#0
U$34: #_IO0#0
U$35: #_GND#0
U$36: #_3V3#0
U$38: #VUSB_#0
U$39: #VBAT_#0
U$40: #EN_#0
U$41: #SD_DET#0
U$42: BOOT0
U$43: RST0
U$44: IO90
U$45, U$47: THING_PLUS0
U$46, U$48: ESP32#C60
U$49, U$50: #MEAS#0
U$51: #CHG#0
U$52: #PWR#0
U$53: PWR0
U$54: CHG0
U$55: STAT0
U$56: #RGB#0
U$57: ORDERING_INSTRUCTIONS
U$58: #RGB_#0
U$59: #_RGB#0
U$62: IO230
U$63: #G#0
U$64: #IO23_#0
U$65: #IO15_#0
U$66: #IO22_#0
